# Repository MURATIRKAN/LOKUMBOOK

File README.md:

LOKUM BOOK PROJESİ
MURAT IRKAN 2024 /02
REV.A

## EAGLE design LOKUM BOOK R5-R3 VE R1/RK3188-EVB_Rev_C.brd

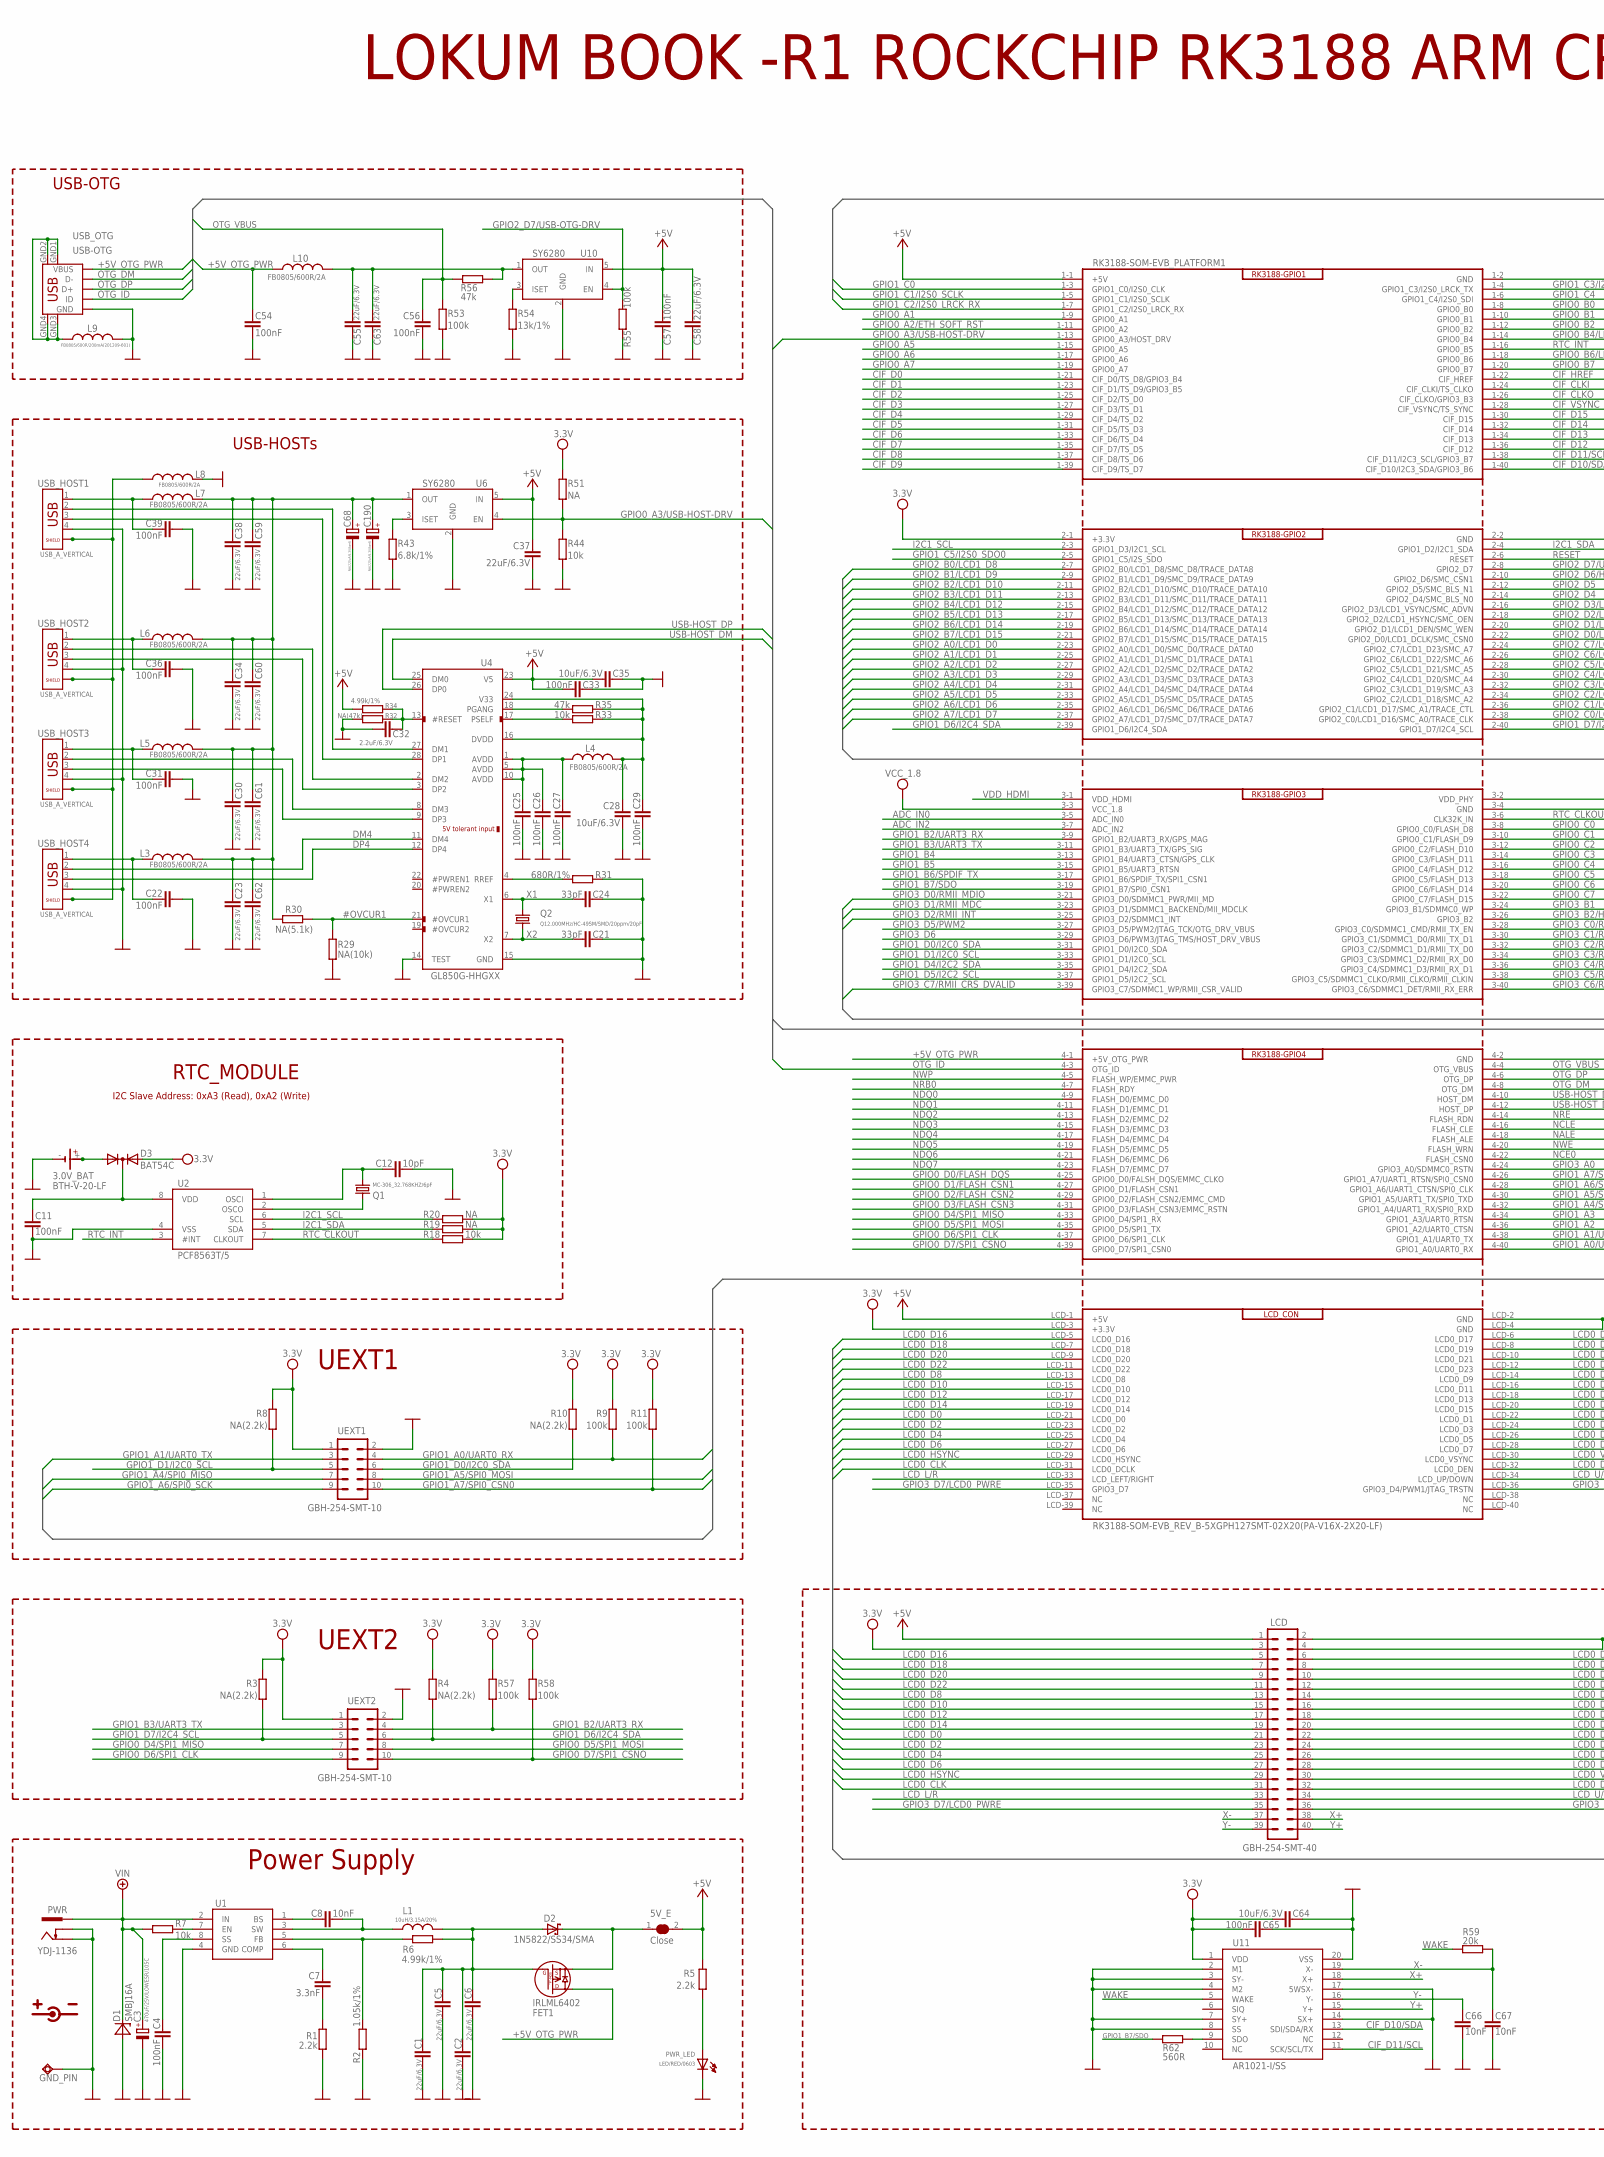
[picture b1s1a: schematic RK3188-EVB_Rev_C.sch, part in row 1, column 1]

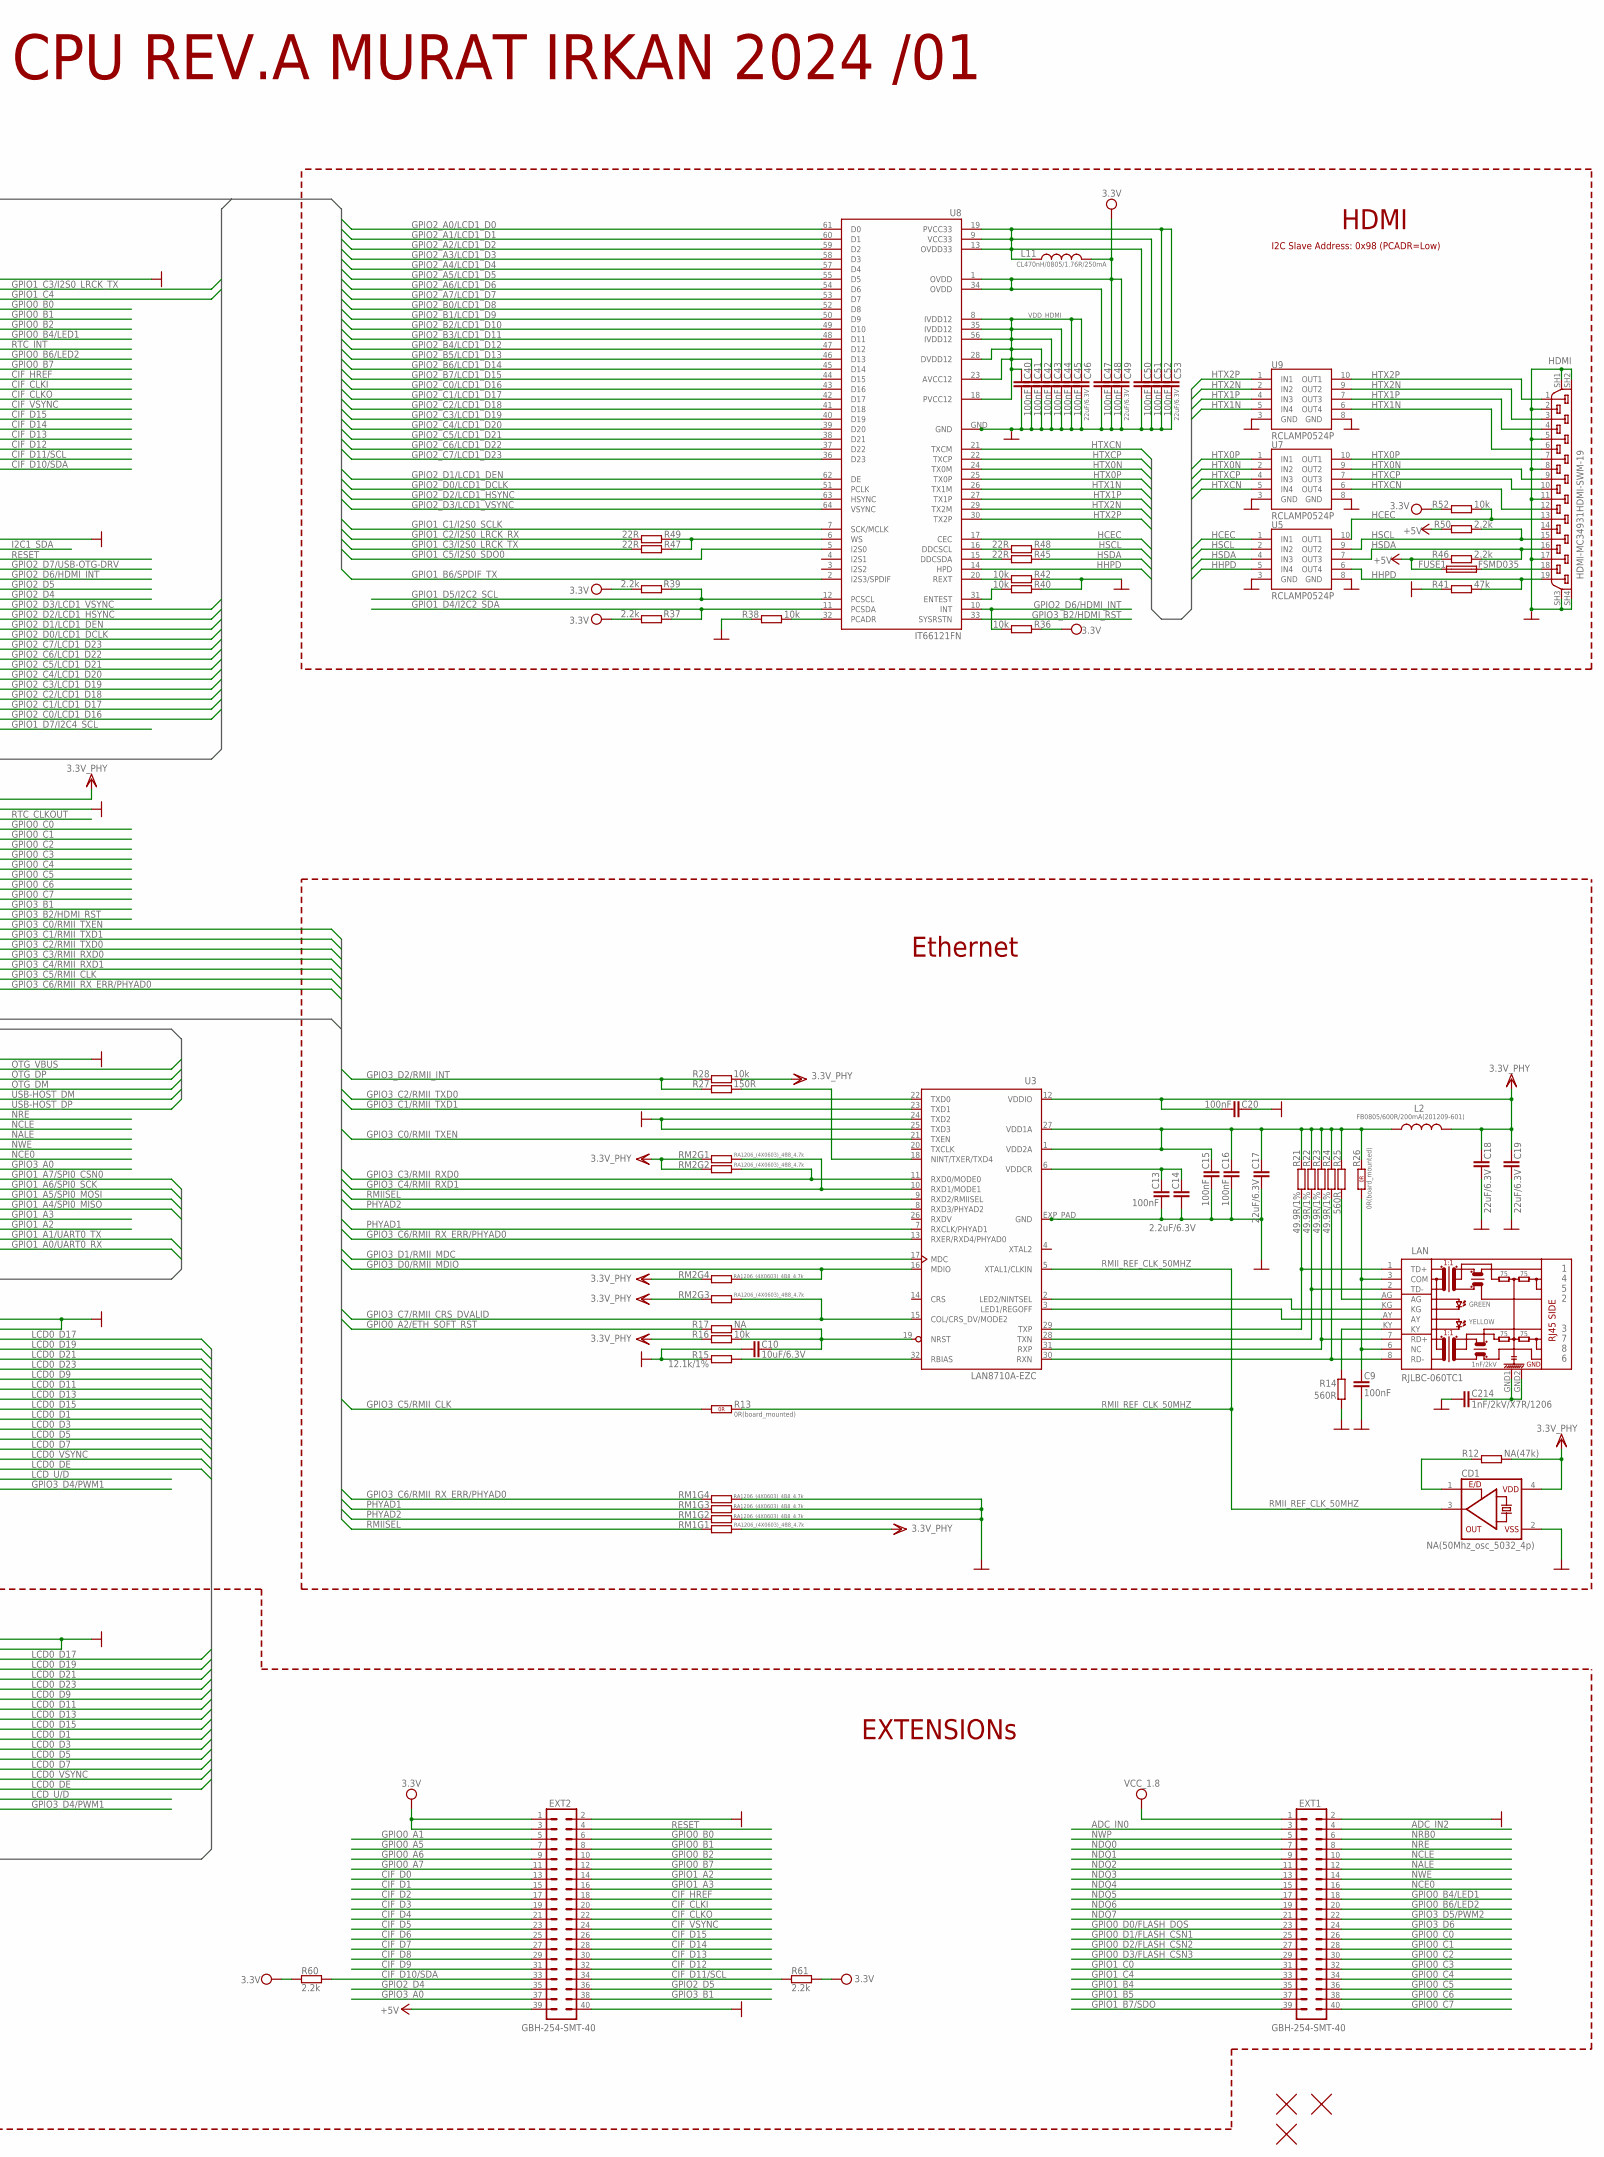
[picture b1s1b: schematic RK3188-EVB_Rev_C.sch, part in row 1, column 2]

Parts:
3.0V_BAT: BTH-V-20-LF; 3V_BAT_HOLDER
5V_E: Close; SJ-CLOSE
C1, C2, C5, C6, C17, C18, C19, C23, C30, C34, C37, C38, C46, C49, C53, C55, C58, C59, C60, C61, C62, C63: 22uF/6.3V; C0603_DWS
C3: 470uF/25V/LOWESR/105C; E5-10,5
C4, C9, C11, C13, C15, C16, C20, C22, C25, C26, C27, C29, C31, C33, C36, C39, C40, C41, C42, C43, C44, C45, C47, C48, C50, C51, C52, C54, C56, C57, C65: 100nF; C0603_DWS
C7: 3.3nF; C0603_DWS
C8, C66, C67: 10nF; C0603_DWS
C10, C28, C35, C64: 10uF/6.3V; C0603_DWS
C12: 10pF; C0603_DWS
C14, C32: 2.2uF/6.3V; C0603_DWS
C21, C24: 33pF; C0603_DWS
C68, C190: NA(220uF/6.3V/tant); CT6032
C214: 1nF/2kV/X7R/1206; C1206_5MILS_WS_ISO
CD1: NA(50Mhz_osc_5032_4p); 5032-4P_HCX-3S
D1: SMBJ16A; DO214AA
D2: 1N5822/SS34/SMA; MLL-41
D3: BAT54C; SOT23C
EXT1, EXT2: GBH-254-SMT-40; ML40-MALE(GBH-254-SMT-40)
FET1: IRLML6402; SOT23
FID1, FID3, FID4: FIDUCIAL; FIDUCIAL-1X3
FUSE1: FSMD035; 1206
GND_PIN: TESTPAD3; TEST_PAD40/70/SQUARE
HDMI: HDMI-MC34931HDMI-SWM-19; HDMI-SWM-19
L1: 10uH/3.15A/20%; 8X8MM_3131
L2, L9: FB0805/600R/200mA(201209-601); L0805_5MIL_DWS
L3, L4, L5, L6, L7, L8, L10: FB0805/600R/2A; L0805_5MIL_DWS
L11: CL470nH/0805/1.76R/250mA; L0805_5MIL_DWS
LAN: RJLBC-060TC1; RJLBC-060TC1_MILLING
LCD: GBH-254-SMT-40; ML40-MALE(GBH-254-SMT-40)
PWR: YDJ-1136; PWR_JACK_UNI_MILLING
PWR_LED: LED/RED/0603; LED-0603
Q1: MC-306_32.768KHZ/6pF; MC-306
Q2: Q12.000MHz/HC-49SM/SMD/20ppm/20pF; HC49/SMD2_THIN
R1, R5, R37, R39, R46, R50, R60, R61: 2.2k; R0603_5MIL_DWS
R2: 1.05k/1%; R0603_5MIL_DWS
R3, R4, R8, R10: NA(2.2k); R0603_5MIL_DWS
R6, R34: 4.99k/1%; R0603_5MIL_DWS
R7, R16, R18, R28, R33, R36, R38, R40, R42, R44, R52: 10k; R0603_5MIL_DWS
R9, R11, R53, R55, R57, R58: 100k; R0603_5MIL_DWS
R12, R32: NA(47k); R0603_5MIL_DWS
R13, R26: 0R(board_mounted); 0603_0R
R14, R25, R62: 560R; R0603_5MIL_DWS
R15: 12.1k/1%; R0603_5MIL_DWS
R17, R19, R20, R51: NA; R0603_5MIL_DWS
R21, R22, R23, R24: 49.9R/1%; R0603_5MIL_DWS
R27: 150R; R0603_5MIL_DWS
R29: NA(10k); R0603_5MIL_DWS
R30: NA(5.1k); R0603_5MIL_DWS
R31: 680R/1%; R0603_5MIL_DWS
R35, R41, R56: 47k; R0603_5MIL_DWS
R43: 6.8k/1%; R0603_5MIL_DWS
R45, R47, R48, R49: 22R; R0603_5MIL_DWS
R54: 13k/1%; R0603_5MIL_DWS
R59: 20k; R0603_5MIL_DWS
RK3188-SOM-EVB_PLATFORM1: RK3188-SOM-EVB_REV_B-5XGPH127SMT-02X20(PA-V16X-2X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; RK3188-SOM-EVB_REV_B
RM1, RM2: RA1206_(4X0603)_4B8_4.7k; R_MATRIX_4
U1: MP1482DS; SOIC8
U2: PCF8563T/5; SO-8
U3: LAN8710A-EZC; QFN-32(DRILLS)
U4: GL850G-HHGXX; SSOP28
U5, U7, U9: RCLAMP0524P; SLP2510P8
U6, U10: SY6280; SOT23-5
U8: IT66121FN; QFN64(IT66121FN)
U11: AR1021-I/SS; SSOP20
UEXT1, UEXT2: GBH-254-SMT-10; ML10_S
USB_HOST1, USB_HOST2, USB_HOST3, USB_HOST4: USB_A_VERTICAL; USB_A_VERTICAL_PTH
USB_OTG: USB-OTG; USB_MINI_9PIN

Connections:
#OVCUR1: R29.2, R30.1, U4.21 (#OVCUR1)
+5V: 5V_E.2, C33.1, C35.1, C37.1, C57.1, C58.1, EXT2.39, FUSE1.1, LCD.1, R5.1, R34.2, R46.2, R50.2, RK3188-SOM-EVB_PLATFORM1.1-1 (+5V), RK3188-SOM-EVB_PLATFORM1.LCD-1 (+5V), U4.23 (V5), U6.5 (IN), U10.5 (IN)
+5V_OTG_PWR: C54.1, FET1.3 (D), L10.1, RK3188-SOM-EVB_PLATFORM1.4-1 (+5V_OTG_PWR), USB_OTG.VBUS
+12V: C3.+, D1.C, PWR.+, R7.1, U1.2 (IN)
ADC_IN0: EXT1.3, RK3188-SOM-EVB_PLATFORM1.3-5 (ADC_IN0)
ADC_IN2: EXT1.4, RK3188-SOM-EVB_PLATFORM1.3-7 (ADC_IN2)
AVDD2: C25.1, C26.1, C27.1, L4.2, U4.1 (AVDD), U4.5 (AVDD), U4.10 (AVDD)
CIF_CLKI: EXT2.20, RK3188-SOM-EVB_PLATFORM1.1-24 (CIF_CLKI/TS_CLKO)
CIF_CLKO: EXT2.22, RK3188-SOM-EVB_PLATFORM1.1-26 (CIF_CLKO/GPIO3_B3)
CIF_D0: EXT2.13, RK3188-SOM-EVB_PLATFORM1.1-21 (CIF_D0/TS_D8/GPIO3_B4)
CIF_D1: EXT2.15, RK3188-SOM-EVB_PLATFORM1.1-23 (CIF_D1/TS_D9/GPIO3_B5)
CIF_D2: EXT2.17, RK3188-SOM-EVB_PLATFORM1.1-25 (CIF_D2/TS_D0)
CIF_D3: EXT2.19, RK3188-SOM-EVB_PLATFORM1.1-27 (CIF_D3/TS_D1)
CIF_D4: EXT2.21, RK3188-SOM-EVB_PLATFORM1.1-29 (CIF_D4/TS_D2)
CIF_D5: EXT2.23, RK3188-SOM-EVB_PLATFORM1.1-31 (CIF_D5/TS_D3)
CIF_D6: EXT2.25, RK3188-SOM-EVB_PLATFORM1.1-33 (CIF_D6/TS_D4)
CIF_D7: EXT2.27, RK3188-SOM-EVB_PLATFORM1.1-35 (CIF_D7/TS_D5)
CIF_D8: EXT2.29, RK3188-SOM-EVB_PLATFORM1.1-37 (CIF_D8/TS_D6)
CIF_D9: EXT2.31, RK3188-SOM-EVB_PLATFORM1.1-39 (CIF_D9/TS_D7)
CIF_D10/SDA: EXT2.33, R60.1, RK3188-SOM-EVB_PLATFORM1.1-40 (CIF_D10/I2C3_SDA/GPIO3_B6), U11.13 (SDI/SDA/RX)
CIF_D11/SCL: EXT2.34, R61.1, RK3188-SOM-EVB_PLATFORM1.1-38 (CIF_D11/I2C3_SCL/GPIO3_B7), U11.11 (SCK/SCL/TX)
CIF_D12: EXT2.32, RK3188-SOM-EVB_PLATFORM1.1-36 (CIF_D12)
CIF_D13: EXT2.30, RK3188-SOM-EVB_PLATFORM1.1-34 (CIF_D13)
CIF_D14: EXT2.28, RK3188-SOM-EVB_PLATFORM1.1-32 (CIF_D14)
CIF_D15: EXT2.26, RK3188-SOM-EVB_PLATFORM1.1-30 (CIF_D15)
CIF_HREF: EXT2.18, RK3188-SOM-EVB_PLATFORM1.1-22 (CIF_HREF)
CIF_VSYNC: EXT2.24, RK3188-SOM-EVB_PLATFORM1.1-28 (CIF_VSYNC/TS_SYNC)
DM1: U4.27 (DM1), USB_HOST1.2
DM2: U4.2 (DM2), USB_HOST2.2
DM3: U4.8 (DM3), USB_HOST3.2
DM4: U4.11 (DM4), USB_HOST4.2
DP1: U4.28 (DP1), USB_HOST1.3
DP2: U4.3 (DP2), USB_HOST2.3
DP3: U4.9 (DP3), USB_HOST3.3
DP4: U4.12 (DP4), USB_HOST4.3
DVDD1: C28.1, C29.1, L4.1, R33.1, R35.1, U4.16 (DVDD), U4.24 (V33)
GND: 3.0V_BAT.-, C1.2, C2.2, C3.-, C4.2, C5.2, C6.2, C9.1, C10.1, C11.1, C12.2, C13.1, C14.1, C15.1, C16.1, C17.1, C18.1, C19.1, C20.1, C21.1, C22.2, C23.1, C24.1, C25.2, C26.2, C27.2, C28.2, C29.2, C30.1, C31.2, C32.1, C33.2, C34.1, C35.2, C36.2, C37.2, C38.1, C39.2, C40.2, C41.2, C42.2, C43.2, C44.2, C45.2, C46.2, C47.2, C48.2, C49.2, C50.2, C51.2, C52.2, C53.2, C54.2, C55.2, C56.2, C57.2, C58.2, C59.1, C60.1, C61.1, C62.1, C63.2, C64.2, C65.2, C66.1, C67.1, C68.-, C190.-, C214.2, CD1.2 (VSS), D1.A, EXT1.2, EXT2.2, EXT2.40, GND_PIN.P$1, HDMI.2, HDMI.5, HDMI.8, HDMI.11, HDMI.17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
GPIO0_A1: EXT2.5, RK3188-SOM-EVB_PLATFORM1.1-9 (GPIO0_A1)
GPIO0_A2/ETH_SOFT_RST: R17.1, RK3188-SOM-EVB_PLATFORM1.1-11 (GPIO0_A2)
GPIO0_A3/USB-HOST-DRV: R44.2, R51.2, RK3188-SOM-EVB_PLATFORM1.1-13 (GPIO0_A3/HOST_DRV), U6.4 (EN)
GPIO0_A5: EXT2.7, RK3188-SOM-EVB_PLATFORM1.1-15 (GPIO0_A5)
GPIO0_A6: EXT2.9, RK3188-SOM-EVB_PLATFORM1.1-17 (GPIO0_A6)
GPIO0_A7: EXT2.11, RK3188-SOM-EVB_PLATFORM1.1-19 (GPIO0_A7)
GPIO0_B0: EXT2.6, RK3188-SOM-EVB_PLATFORM1.1-8 (GPIO0_B0)
GPIO0_B1: EXT2.8, RK3188-SOM-EVB_PLATFORM1.1-10 (GPIO0_B1)
GPIO0_B2: EXT2.10, RK3188-SOM-EVB_PLATFORM1.1-12 (GPIO0_B2)
GPIO0_B4/LED1: EXT1.18, RK3188-SOM-EVB_PLATFORM1.1-14 (GPIO0_B4)
GPIO0_B6/LED2: EXT1.20, RK3188-SOM-EVB_PLATFORM1.1-18 (GPIO0_B6)
GPIO0_B7: EXT2.12, RK3188-SOM-EVB_PLATFORM1.1-20 (GPIO0_B7)
GPIO0_C0: EXT1.26, RK3188-SOM-EVB_PLATFORM1.3-8 (GPIO0_C0/FLASH_D8)
GPIO0_C1: EXT1.28, RK3188-SOM-EVB_PLATFORM1.3-10 (GPIO0_C1/FLASH_D9)
GPIO0_C2: EXT1.30, RK3188-SOM-EVB_PLATFORM1.3-12 (GPIO0_C2/FLASH_D10)
GPIO0_C3: EXT1.32, RK3188-SOM-EVB_PLATFORM1.3-14 (GPIO0_C3/FLASH_D11)
GPIO0_C4: EXT1.34, RK3188-SOM-EVB_PLATFORM1.3-16 (GPIO0_C4/FLASH_D12)
GPIO0_C5: EXT1.36, RK3188-SOM-EVB_PLATFORM1.3-18 (GPIO0_C5/FLASH_D13)
GPIO0_C6: EXT1.38, RK3188-SOM-EVB_PLATFORM1.3-20 (GPIO0_C6/FLASH_D14)
GPIO0_C7: EXT1.40, RK3188-SOM-EVB_PLATFORM1.3-22 (GPIO0_C7/FLASH_D15)
GPIO0_D0/FLASH_DQS: EXT1.23, RK3188-SOM-EVB_PLATFORM1.4-25 (GPIO0_D0/FALSH_DQS/EMMC_CLKO)
GPIO0_D1/FLASH_CSN1: EXT1.25, RK3188-SOM-EVB_PLATFORM1.4-27 (GPIO0_D1/FLASH_CSN1)
GPIO0_D2/FLASH_CSN2: EXT1.27, RK3188-SOM-EVB_PLATFORM1.4-29 (GPIO0_D2/FLASH_CSN2/EMMC_CMD)
GPIO0_D3/FLASH_CSN3: EXT1.29, RK3188-SOM-EVB_PLATFORM1.4-31 (GPIO0_D3/FLASH_CSN3/EMMC_RSTN)
GPIO0_D4/SPI1_MISO: RK3188-SOM-EVB_PLATFORM1.4-33 (GPIO0_D4/SPI1_RX), UEXT2.7
GPIO0_D5/SPI1_MOSI: RK3188-SOM-EVB_PLATFORM1.4-35 (GPIO0_D5/SPI1_TX), UEXT2.8
GPIO0_D6/SPI1_CLK: RK3188-SOM-EVB_PLATFORM1.4-37 (GPIO0_D6/SPI1_CLK), UEXT2.9
GPIO0_D7/SPI1_CSNO: R58.1, RK3188-SOM-EVB_PLATFORM1.4-39 (GPIO0_D7/SPI1_CSN0), UEXT2.10
GPIO1_A0/UART0_RX: R9.1, RK3188-SOM-EVB_PLATFORM1.4-40 (GPIO1_A0/UART0_RX), UEXT1.4
GPIO1_A1/UART0_TX: RK3188-SOM-EVB_PLATFORM1.4-38 (GPIO1_A1/UART0_TX), UEXT1.3
GPIO1_A2: EXT2.14, RK3188-SOM-EVB_PLATFORM1.4-36 (GPIO1_A2/UART0_CTSN)
GPIO1_A3: EXT2.16, RK3188-SOM-EVB_PLATFORM1.4-34 (GPIO1_A3/UART0_RTSN)
GPIO1_A4/SPI0_MISO: RK3188-SOM-EVB_PLATFORM1.4-32 (GPIO1_A4/UART1_RX/SPI0_RXD), UEXT1.7
GPIO1_A5/SPI0_MOSI: RK3188-SOM-EVB_PLATFORM1.4-30 (GPIO1_A5/UART1_TX/SPI0_TXD), UEXT1.8
GPIO1_A6/SPI0_SCK: RK3188-SOM-EVB_PLATFORM1.4-28 (GPIO1_A6/UART1_CTSN/SPI0_CLK), UEXT1.9
GPIO1_A7/SPI0_CSN0: R11.1, RK3188-SOM-EVB_PLATFORM1.4-26 (GPIO1_A7/UART1_RTSN/SPI0_CSN0), UEXT1.10
GPIO1_B2/UART3_RX: R57.1, RK3188-SOM-EVB_PLATFORM1.3-9 (GPIO1_B2/UART3_RX/GPS_MAG), UEXT2.4
GPIO1_B3/UART3_TX: RK3188-SOM-EVB_PLATFORM1.3-11 (GPIO1_B3/UART3_TX/GPS_SIG), UEXT2.3
GPIO1_B4: EXT1.35, RK3188-SOM-EVB_PLATFORM1.3-13 (GPIO1_B4/UART3_CTSN/GPS_CLK)
GPIO1_B5: EXT1.37, RK3188-SOM-EVB_PLATFORM1.3-15 (GPIO1_B5/UART3_RTSN)
GPIO1_B6/SPDIF_TX: RK3188-SOM-EVB_PLATFORM1.3-17 (GPIO1_B6/SPDIF_TX/SPI1_CSN1), U8.2 (I2S3/SPDIF)
GPIO1_B7/SDO: EXT1.39, R62.2, RK3188-SOM-EVB_PLATFORM1.3-19 (GPIO1_B7/SPI0_CSN1)
GPIO1_C0: EXT1.31, RK3188-SOM-EVB_PLATFORM1.1-3 (GPIO1_C0/I2S0_CLK)
GPIO1_C1/I2S0_SCLK: RK3188-SOM-EVB_PLATFORM1.1-5 (GPIO1_C1/I2S0_SCLK), U8.7 (SCK/MCLK)
GPIO1_C2/I2S0_LRCK_RX: R49.1, RK3188-SOM-EVB_PLATFORM1.1-7 (GPIO1_C2/I2S0_LRCK_RX)
GPIO1_C3/I2S0_LRCK_TX: R47.1, RK3188-SOM-EVB_PLATFORM1.1-4 (GPIO1_C3/I2S0_LRCK_TX)
GPIO1_C4: EXT1.33, RK3188-SOM-EVB_PLATFORM1.1-6 (GPIO1_C4/I2S0_SDI)
GPIO1_C5/I2S0_SDO0: RK3188-SOM-EVB_PLATFORM1.2-5 (GPIO1_C5/I2S_SDO), U8.5 (I2S0)
GPIO1_D0/I2C0_SDA: R10.1, RK3188-SOM-EVB_PLATFORM1.3-31 (GPIO1_D0/I2C0_SDA), UEXT1.6
GPIO1_D1/I2C0_SCL: R8.1, RK3188-SOM-EVB_PLATFORM1.3-33 (GPIO1_D1/I2C0_SCL), UEXT1.5
GPIO1_D4/I2C2_SDA: R37.1, RK3188-SOM-EVB_PLATFORM1.3-35 (GPIO1_D4/I2C2_SDA), U8.11 (PCSDA)
GPIO1_D5/I2C2_SCL: R39.1, RK3188-SOM-EVB_PLATFORM1.3-37 (GPIO1_D5/I2C2_SCL), U8.12 (PCSCL)
GPIO1_D6/I2C4_SDA: R4.1, RK3188-SOM-EVB_PLATFORM1.2-39 (GPIO1_D6/I2C4_SDA), UEXT2.6
GPIO1_D7/I2C4_SCL: R3.1, RK3188-SOM-EVB_PLATFORM1.2-40 (GPIO1_D7/I2C4_SCL), UEXT2.5
GPIO2_A0/LCD1_D0: RK3188-SOM-EVB_PLATFORM1.2-23 (GPIO2_A0/LCD1_D0/SMC_D0/TRACE_DATA0), U8.61 (D0)
GPIO2_A1/LCD1_D1: RK3188-SOM-EVB_PLATFORM1.2-25 (GPIO2_A1/LCD1_D1/SMC_D1/TRACE_DATA1), U8.60 (D1)
GPIO2_A2/LCD1_D2: RK3188-SOM-EVB_PLATFORM1.2-27 (GPIO2_A2/LCD1_D2/SMC_D2/TRACE_DATA2), U8.59 (D2)
GPIO2_A3/LCD1_D3: RK3188-SOM-EVB_PLATFORM1.2-29 (GPIO2_A3/LCD1_D3/SMC_D3/TRACE_DATA3), U8.58 (D3)
GPIO2_A4/LCD1_D4: RK3188-SOM-EVB_PLATFORM1.2-31 (GPIO2_A4/LCD1_D4/SMC_D4/TRACE_DATA4), U8.57 (D4)
GPIO2_A5/LCD1_D5: RK3188-SOM-EVB_PLATFORM1.2-33 (GPIO2_A5/LCD1_D5/SMC_D5/TRACE_DATA5), U8.55 (D5)
GPIO2_A6/LCD1_D6: RK3188-SOM-EVB_PLATFORM1.2-35 (GPIO2_A6/LCD1_D6/SMC_D6/TRACE_DATA6), U8.54 (D6)
GPIO2_A7/LCD1_D7: RK3188-SOM-EVB_PLATFORM1.2-37 (GPIO2_A7/LCD1_D7/SMC_D7/TRACE_DATA7), U8.53 (D7)
GPIO2_B0/LCD1_D8: RK3188-SOM-EVB_PLATFORM1.2-7 (GPIO2_B0/LCD1_D8/SMC_D8/TRACE_DATA8), U8.52 (D8)
GPIO2_B1/LCD1_D9: RK3188-SOM-EVB_PLATFORM1.2-9 (GPIO2_B1/LCD1_D9/SMC_D9/TRACE_DATA9), U8.50 (D9)
GPIO2_B2/LCD1_D10: RK3188-SOM-EVB_PLATFORM1.2-11 (GPIO2_B2/LCD1_D10/SMC_D10/TRACE_DATA10), U8.49 (D10)
GPIO2_B3/LCD1_D11: RK3188-SOM-EVB_PLATFORM1.2-13 (GPIO2_B3/LCD1_D11/SMC_D11/TRACE_DATA11), U8.48 (D11)
GPIO2_B4/LCD1_D12: RK3188-SOM-EVB_PLATFORM1.2-15 (GPIO2_B4/LCD1_D12/SMC_D12/TRACE_DATA12), U8.47 (D12)
GPIO2_B5/LCD1_D13: RK3188-SOM-EVB_PLATFORM1.2-17 (GPIO2_B5/LCD1_D13/SMC_D13/TRACE_DATA13), U8.46 (D13)
GPIO2_B6/LCD1_D14: RK3188-SOM-EVB_PLATFORM1.2-19 (GPIO2_B6/LCD1_D14/SMC_D14/TRACE_DATA14), U8.45 (D14)
GPIO2_B7/LCD1_D15: RK3188-SOM-EVB_PLATFORM1.2-21 (GPIO2_B7/LCD1_D15/SMC_D15/TRACE_DATA15), U8.44 (D15)
GPIO2_C0/LCD1_D16: RK3188-SOM-EVB_PLATFORM1.2-38 (GPIO2_C0/LCD1_D16/SMC_A0/TRACE_CLK), U8.43 (D16)
GPIO2_C1/LCD1_D17: RK3188-SOM-EVB_PLATFORM1.2-36 (GPIO2_C1/LCD1_D17/SMC_A1/TRACE_CTL), U8.42 (D17)
GPIO2_C2/LCD1_D18: RK3188-SOM-EVB_PLATFORM1.2-34 (GPIO2_C2/LCD1_D18/SMC_A2), U8.41 (D18)
GPIO2_C3/LCD1_D19: RK3188-SOM-EVB_PLATFORM1.2-32 (GPIO2_C3/LCD1_D19/SMC_A3), U8.40 (D19)
GPIO2_C4/LCD1_D20: RK3188-SOM-EVB_PLATFORM1.2-30 (GPIO2_C4/LCD1_D20/SMC_A4), U8.39 (D20)
GPIO2_C5/LCD1_D21: RK3188-SOM-EVB_PLATFORM1.2-28 (GPIO2_C5/LCD1_D21/SMC_A5), U8.38 (D21)
GPIO2_C6/LCD1_D22: RK3188-SOM-EVB_PLATFORM1.2-26 (GPIO2_C6/LCD1_D22/SMC_A6), U8.37 (D22)
GPIO2_C7/LCD1_D23: RK3188-SOM-EVB_PLATFORM1.2-24 (GPIO2_C7/LCD1_D23/SMC_A7), U8.36 (D23)
GPIO2_D0/LCD1_DCLK: RK3188-SOM-EVB_PLATFORM1.2-22 (GPIO2_D0/LCD1_DCLK/SMC_CSN0), U8.51 (PCLK)
GPIO2_D1/LCD1_DEN: RK3188-SOM-EVB_PLATFORM1.2-20 (GPIO2_D1/LCD1_DEN/SMC_WEN), U8.62 (DE)
GPIO2_D2/LCD1_HSYNC: RK3188-SOM-EVB_PLATFORM1.2-18 (GPIO2_D2/LCD1_HSYNC/SMC_OEN), U8.63 (HSYNC)
GPIO2_D3/LCD1_VSYNC: RK3188-SOM-EVB_PLATFORM1.2-16 (GPIO2_D3/LCD1_VSYNC/SMC_ADVN), U8.64 (VSYNC)
GPIO2_D4: EXT2.35, RK3188-SOM-EVB_PLATFORM1.2-14 (GPIO2_D4/SMC_BLS_N0)
GPIO2_D5: EXT2.36, RK3188-SOM-EVB_PLATFORM1.2-12 (GPIO2_D5/SMC_BLS_N1)
GPIO2_D6/HDMI_INT: R36.1, RK3188-SOM-EVB_PLATFORM1.2-10 (GPIO2_D6/SMC_CSN1), U8.10 (INT)
GPIO2_D7/USB-OTG-DRV: R55.2, RK3188-SOM-EVB_PLATFORM1.2-8 (GPIO2_D7), U10.4 (EN)
GPIO3_A0: EXT2.37, RK3188-SOM-EVB_PLATFORM1.4-24 (GPIO3_A0/SDMMC0_RSTN)
GPIO3_B1: EXT2.38, RK3188-SOM-EVB_PLATFORM1.3-24 (GPIO3_B1/SDMMC0_WP)
GPIO3_B2/HDMI_RST: RK3188-SOM-EVB_PLATFORM1.3-26 (GPIO3_B2), U8.33 (SYSRSTN)
GPIO3_C0/RMII_TXEN: RK3188-SOM-EVB_PLATFORM1.3-28 (GPIO3_C0/SDMMC1_CMD/RMII_TX_EN), U3.21 (TXEN)
GPIO3_C1/RMII_TXD1: RK3188-SOM-EVB_PLATFORM1.3-30 (GPIO3_C1/SDMMC1_D0/RMII_TX_D1), U3.23 (TXD1)
GPIO3_C2/RMII_TXD0: RK3188-SOM-EVB_PLATFORM1.3-32 (GPIO3_C2/SDMMC1_D1/RMII_TX_D0), U3.22 (TXD0)
GPIO3_C3/RMII_RXD0: RK3188-SOM-EVB_PLATFORM1.3-34 (GPIO3_C3/SDMMC1_D2/RMII_RX_D0), RM2.2.2 (2), U3.11 (RXD0/MODE0)
GPIO3_C4/RMII_RXD1: RK3188-SOM-EVB_PLATFORM1.3-36 (GPIO3_C4/SDMMC1_D3/RMII_RX_D1), RM2.1.2 (2), U3.10 (RXD1/MODE1)
GPIO3_C5/RMII_CLK: R13.1 (1.1), RK3188-SOM-EVB_PLATFORM1.3-38 (GPIO3_C5/SDMMC1_CLKO/RMII_CLKO/RMII_CLK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)
GPIO3_C6/RMII_RX_ERR/PHYAD0: RK3188-SOM-EVB_PLATFORM1.3-40 (GPIO3_C6/SDMMC1_DET/RMII_RX_ERR), RM1.4.1 (1), U3.13 (RXER/RXD4/PHYAD0)
GPIO3_C7/RMII_CRS_DVALID: RK3188-SOM-EVB_PLATFORM1.3-39 (GPIO3_C7/SDMMC1_WP/RMII_CSR_VALID), RM2.3.2 (2), U3.15 (COL/CRS_DV/MODE2)
GPIO3_D0/RMII_MDIO: RK3188-SOM-EVB_PLATFORM1.3-21 (GPIO3_D0/SDMMC1_PWR/MII_MD), RM2.4.2 (2), U3.16 (MDIO)
GPIO3_D1/RMII_MDC: RK3188-SOM-EVB_PLATFORM1.3-23 (GPIO3_D1/SDMMC1_BACKEND/MII_MDCLK), U3.17 (MDC)
GPIO3_D2/RMII_INT: R27.1, R28.1, RK3188-SOM-EVB_PLATFORM1.3-25 (GPIO3_D2/SDMMC1_INT)
GPIO3_D4/PWM1: LCD.36, RK3188-SOM-EVB_PLATFORM1.LCD-36 (GPIO3_D4/PWM1/JTAG_TRSTN)
GPIO3_D5/PWM2: EXT1.22, RK3188-SOM-EVB_PLATFORM1.3-27 (GPIO3_D5/PWM2/JTAG_TCK/OTG_DRV_VBUS)
GPIO3_D6: EXT1.24, RK3188-SOM-EVB_PLATFORM1.3-29 (GPIO3_D6/PWM3/JTAG_TMS/HOST_DRV_VBUS)
GPIO3_D7/LCD0_PWRE: LCD.35, RK3188-SOM-EVB_PLATFORM1.LCD-35 (GPIO3_D7)
HCEC: HDMI.13, R52.1, U5.1 (IN1), U5.10 (OUT1), U8.17 (CEC)
HDMI_5V_SOURCE: FUSE1.2, HDMI.18
HHPD: HDMI.19, R41.1, U5.5 (IN4), U5.6 (OUT4), U8.14 (HPD)
HSCL: HDMI.15, R48.1, R50.1, U5.2 (IN2), U5.9 (OUT2)
HSDA: HDMI.16, R45.1, R46.1, U5.4 (IN3), U5.7 (OUT3)
HTX0N: HDMI.9, U7.2 (IN2), U7.9 (OUT2), U8.24 (TX0M)
HTX0P: HDMI.7, U7.1 (IN1), U7.10 (OUT1), U8.25 (TX0P)
HTX1N: HDMI.6, U8.26 (TX1M), U9.5 (IN4), U9.6 (OUT4)
HTX1P: HDMI.4, U8.27 (TX1P), U9.4 (IN3), U9.7 (OUT3)
HTX2N: HDMI.3, U8.29 (TX2M), U9.2 (IN2), U9.9 (OUT2)
HTX2P: HDMI.1, U8.30 (TX2P), U9.1 (IN1), U9.10 (OUT1)
HTXCN: HDMI.12, U7.5 (IN4), U7.6 (OUT4), U8.21 (TXCM)
HTXCP: HDMI.10, U7.4 (IN3), U7.7 (OUT3), U8.22 (TXCP)
I2C1_SCL: R20.1, RK3188-SOM-EVB_PLATFORM1.2-3 (GPIO1_D3/I2C1_SCL), U2.6 (SCL)
I2C1_SDA: R19.1, RK3188-SOM-EVB_PLATFORM1.2-4 (GPIO1_D2/I2C1_SDA), U2.5 (SDA)
I2S0_LRCK: R47.2, R49.2, U8.6 (WS)
LCD0_CLK: LCD.31, RK3188-SOM-EVB_PLATFORM1.LCD-31 (LCD0_DCLK)
LCD0_D0: LCD.21, RK3188-SOM-EVB_PLATFORM1.LCD-21 (LCD0_D0)
LCD0_D1: LCD.22, RK3188-SOM-EVB_PLATFORM1.LCD-22 (LCD0_D1)
LCD0_D2: LCD.23, RK3188-SOM-EVB_PLATFORM1.LCD-23 (LCD0_D2)
LCD0_D3: LCD.24, RK3188-SOM-EVB_PLATFORM1.LCD-24 (LCD0_D3)
LCD0_D4: LCD.25, RK3188-SOM-EVB_PLATFORM1.LCD-25 (LCD0_D4)
LCD0_D5: LCD.26, RK3188-SOM-EVB_PLATFORM1.LCD-26 (LCD0_D5)
LCD0_D6: LCD.27, RK3188-SOM-EVB_PLATFORM1.LCD-27 (LCD0_D6)
LCD0_D7: LCD.28, RK3188-SOM-EVB_PLATFORM1.LCD-28 (LCD0_D7)
LCD0_D8: LCD.13, RK3188-SOM-EVB_PLATFORM1.LCD-13 (LCD0_D8)
LCD0_D9: LCD.14, RK3188-SOM-EVB_PLATFORM1.LCD-14 (LCD0_D9)
LCD0_D10: LCD.15, RK3188-SOM-EVB_PLATFORM1.LCD-15 (LCD0_D10)
LCD0_D11: LCD.16, RK3188-SOM-EVB_PLATFORM1.LCD-16 (LCD0_D11)
LCD0_D12: LCD.17, RK3188-SOM-EVB_PLATFORM1.LCD-17 (LCD0_D12)
LCD0_D13: LCD.18, RK3188-SOM-EVB_PLATFORM1.LCD-18 (LCD0_D13)
LCD0_D14: LCD.19, RK3188-SOM-EVB_PLATFORM1.LCD-19 (LCD0_D14)
LCD0_D15: LCD.20, RK3188-SOM-EVB_PLATFORM1.LCD-20 (LCD0_D15)
LCD0_D16: LCD.5, RK3188-SOM-EVB_PLATFORM1.LCD-5 (LCD0_D16)
LCD0_D17: LCD.6, RK3188-SOM-EVB_PLATFORM1.LCD-6 (LCD0_D17)
LCD0_D18: LCD.7, RK3188-SOM-EVB_PLATFORM1.LCD-7 (LCD0_D18)
LCD0_D19: LCD.8, RK3188-SOM-EVB_PLATFORM1.LCD-8 (LCD0_D19)
LCD0_D20: LCD.9, RK3188-SOM-EVB_PLATFORM1.LCD-9 (LCD0_D20)
LCD0_D21: LCD.10, RK3188-SOM-EVB_PLATFORM1.LCD-10 (LCD0_D21)
LCD0_D22: LCD.11, RK3188-SOM-EVB_PLATFORM1.LCD-11 (LCD0_D22)
LCD0_D23: LCD.12, RK3188-SOM-EVB_PLATFORM1.LCD-12 (LCD0_D23)
LCD0_DE: LCD.32, RK3188-SOM-EVB_PLATFORM1.LCD-32 (LCD0_DEN)
LCD0_HSYNC: LCD.29, RK3188-SOM-EVB_PLATFORM1.LCD-29 (LCD0_HSYNC)
LCD0_VSYNC: LCD.30, RK3188-SOM-EVB_PLATFORM1.LCD-30 (LCD0_VSYNC)
LCD_L/R: LCD.33, RK3188-SOM-EVB_PLATFORM1.LCD-33 (LCD_LEFT/RIGHT)
LCD_U/D: LCD.34, RK3188-SOM-EVB_PLATFORM1.LCD-34 (LCD_UP/DOWN)
unnamed: R62.1, U11.9 (SDO)
unnamed: C214.1, LAN.GND1, LAN.GND2
unnamed: CD1.1 (E/D), R12.2
unnamed: LAN.2 (TD-), R22.1, U3.28 (TXN)
unnamed: LAN.KG, U3.2 (LED2/NINTSEL)
unnamed: C13.2, C14.2, U3.6 (VDDCR)
unnamed: C10.2, R16.2, R17.2, U3.19 (NRST)
unnamed: R43.2, U6.3 (ISET)
unnamed: R31.2, U4.4 (RREF)
unnamed: C39.1, L7.2, USB_HOST1.1
unnamed: R42.1, U8.20 (REXT)
unnamed: R40.1, U8.31 (ENTEST)
unnamed: C32.2, R32.1, R34.1, U4.13 (#RESET)
unnamed: L8.2, USB_HOST1.P$3 (5), USB_HOST1.P$4 (6), USB_HOST2.P$3 (5), USB_HOST2.P$4 (6), USB_HOST3.P$3 (5), USB_HOST3.P$4 (6), USB_HOST4.P$3 (5), USB_HOST4.P$4 (6)
unnamed: C22.1, L3.2, USB_HOST4.1
unnamed: C23.2, C30.2, C34.2, C38.2, C59.2, C60.2, C61.2, C62.2, C68.+, C190.+, L3.1, L5.1, L6.1, L7.1, R30.2, U6.1 (OUT)
unnamed: LAN.1 (TD+), R21.1, U3.29 (TXP)
unnamed: LAN.7 (RD+), R23.1, U3.31 (RXP)
unnamed: C4.1, U1.8 (SS)
unnamed: R7.2, U1.7 (EN)
unnamed: C36.1, L6.2, USB_HOST2.1
unnamed: C31.1, L5.2, USB_HOST3.1
unnamed: LAN.8 (RD-), R24.1, U3.30 (RXN)
unnamed: R33.2, U4.17 (PSELF)
unnamed: C8.1, U1.1 (BS)
unnamed: C8.2, L1.1, U1.3 (SW)
unnamed: C50.1, C51.1, C52.1, C53.1, L11.2, U8.9 (VCC33), U8.13 (OVDD33), U8.19 (PVCC33)
unnamed: LAN.AY, U3.3 (LED1/REGOFF)
unnamed: R15.2, U3.32 (RBIAS)
unnamed: C9.2, LAN.3 (COM), LAN.6 (NC), R26.1 (1.1)
unnamed: LAN.KY, R14.1
unnamed: C15.2, C16.2, C17.2, L2.1, R21.2, R22.2, R23.2, R24.2, R25.1, R26.2 (1.2), U3.1 (VDD2A), U3.27 (VDD1A)
unnamed: C7.1, U1.6 (COMP)
unnamed: R48.2, U8.16 (DDCSCL)
unnamed: R45.2, U8.15 (DDCSDA)
unnamed: R27.2, U3.18 (NINT/TXER/TXD4)
unnamed: C7.2, R1.1
unnamed: LAN.AG, R25.2
unnamed: R2.1, R6.1, U1.5 (FB)
unnamed: C1.1, C2.1, C5.1, C6.1, D2.A, FET1.1 (G), L1.2, R6.2
unnamed: 5V_E.1, D2.K (C), FET1.2 (S)
unnamed: R38.1, U8.32 (PCADR)
unnamed: R35.2, U4.18 (PGANG)
unnamed: R54.2, U10.3 (ISET)
unnamed: C12.1, Q1.1, U2.1 (OSCI)
unnamed: PWR_LED.A, R5.2
unnamed: Q1.4 (2), U2.2 (OSCO)
unnamed: 3.0V_BAT.1+ (+), 3.0V_BAT.+, D3.2 (A2)
unnamed: C55.1, C63.1, L10.2, R56.2, U10.1 (OUT)
unnamed: L9.2, USB_OTG.GND1, USB_OTG.GND2, USB_OTG.GND3, USB_OTG.GND4
NALE: EXT1.12, RK3188-SOM-EVB_PLATFORM1.4-18 (FLASH_ALE)
NCE0: EXT1.16, RK3188-SOM-EVB_PLATFORM1.4-22 (FLASH_CSN0)
NCLE: EXT1.10, RK3188-SOM-EVB_PLATFORM1.4-16 (FLASH_CLE)
NDQ0: EXT1.7, RK3188-SOM-EVB_PLATFORM1.4-9 (FLASH_D0/EMMC_D0)
NDQ1: EXT1.9, RK3188-SOM-EVB_PLATFORM1.4-11 (FLASH_D1/EMMC_D1)
NDQ2: EXT1.11, RK3188-SOM-EVB_PLATFORM1.4-13 (FLASH_D2/EMMC_D2)
NDQ3: EXT1.13, RK3188-SOM-EVB_PLATFORM1.4-15 (FLASH_D3/EMMC_D3)
NDQ4: EXT1.15, RK3188-SOM-EVB_PLATFORM1.4-17 (FLASH_D4/EMMC_D4)
NDQ5: EXT1.17, RK3188-SOM-EVB_PLATFORM1.4-19 (FLASH_D5/EMMC_D5)
NDQ6: EXT1.19, RK3188-SOM-EVB_PLATFORM1.4-21 (FLASH_D6/EMMC_D6)
NDQ7: EXT1.21, RK3188-SOM-EVB_PLATFORM1.4-23 (FLASH_D7/EMMC_D7)
NRB0: EXT1.6, RK3188-SOM-EVB_PLATFORM1.4-7 (FLASH_RDY)
NRE: EXT1.8, RK3188-SOM-EVB_PLATFORM1.4-14 (FLASH_RDN)
NWE: EXT1.14, RK3188-SOM-EVB_PLATFORM1.4-20 (FLASH_WRN)
NWP: EXT1.5, RK3188-SOM-EVB_PLATFORM1.4-5 (FLASH_WP/EMMC_PWR)
OTG_DM: RK3188-SOM-EVB_PLATFORM1.4-8 (OTG_DM), USB_OTG.D-
OTG_DP: RK3188-SOM-EVB_PLATFORM1.4-6 (OTG_DP), USB_OTG.D+
OTG_ID: RK3188-SOM-EVB_PLATFORM1.4-3 (OTG_ID), USB_OTG.ID
OTG_VBUS: C56.1, R53.2, R56.1, RK3188-SOM-EVB_PLATFORM1.4-4 (OTG_VBUS)
PHYAD1: RM1.3.1 (1), U3.7 (RXCLK/PHYAD1)
PHYAD2: RM1.2.1 (1), U3.8 (RXD3/PHYAD2)
RESET: EXT2.4, RK3188-SOM-EVB_PLATFORM1.2-6 (RESET)
RMIISEL: RM1.1.1 (1), U3.9 (RXD2/RMIISEL)
RMII_REF_CLK_50MHZ: CD1.3 (OUT), R13.2 (1.2), U3.5 (XTAL1/CLKIN)
RTC_CLKOUT: R18.1, RK3188-SOM-EVB_PLATFORM1.3-6 (CLK32K_IN), U2.7 (CLKOUT)
RTC_INT: RK3188-SOM-EVB_PLATFORM1.1-16 (GPIO0_B5), U2.3 (#INT)
RTC_VDD: C11.2, D3.3 (K), U2.8 (VDD)
USB-HOST_DM: RK3188-SOM-EVB_PLATFORM1.4-10 (HOST_DM), U4.25 (DM0)
USB-HOST_DP: RK3188-SOM-EVB_PLATFORM1.4-12 (HOST_DP), U4.26 (DP0)
VCC: C47.1, C48.1, C49.1, C64.1, C65.1, D3.1 (A1), EXT2.1, EXT2.3, L11.1, LCD.3, R3.2, R4.2, R8.2, R9.2, R10.2, R11.2, R18.2, R19.2, R20.2, R36.2, R37.2, R39.2, R51.1, R52.2, R57.2, R58.2, R60.2, R61.2, RK3188-SOM-EVB_PLATFORM1.2-1 (+3.3V), RK3188-SOM-EVB_PLATFORM1.LCD-3 (+3.3V), U8.1 (OVDD), U8.34 (OVDD), U11.1 (VDD), UEXT1.1, UEXT2.1
VDD: C18.2, C19.2, C20.2, CD1.4 (VDD), L2.2, R12.1, R16.1, R28.2, RK3188-SOM-EVB_PLATFORM1.3-2 (VDD_PHY), RM1.1.2 (2), RM2.1.1 (1), RM2.2.1 (1), RM2.3.1 (1), RM2.4.1 (1), U3.12 (VDDIO)
VDD_HDMI: C40.1, C41.1, C42.1, C43.1, C44.1, C45.1, C46.1, RK3188-SOM-EVB_PLATFORM1.3-1 (VDD_HDMI), U8.8 (IVDD12), U8.18 (PVCC12), U8.23 (AVCC12), U8.28 (DVDD12), U8.35 (IVDD12), U8.56 (IVDD12)
VPP: EXT1.1, RK3188-SOM-EVB_PLATFORM1.3-3 (VCC_1.8)
WAKE: R59.1, U11.5 (WAKE)
X1: C24.2, Q2.2, U4.6 (X1)
X2: C21.2, Q2.1, U4.7 (X2)
X+: LCD.38, U11.18 (X+)
X-: C67.2, LCD.37, R59.2, U11.19 (X-)
Y+: LCD.40, U11.15 (Y+)
Y-: C66.2, LCD.39, U11.16 (Y-)

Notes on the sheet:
EXTENSIONs
RTC_MODULE
USB-OTG
HDMI
Ethernet
I2C Slave Address: 0x98 (PCADR=Low)
USB-HOSTs
Power Supply
I2C Slave Address: 0xA3 (Read), 0xA2 (Write)
UEXT1
UEXT2
LOKUM BOOK -R1 ROCKCHIP RK3188 ARM CPU REV.A MURAT IRKAN 2024 /01

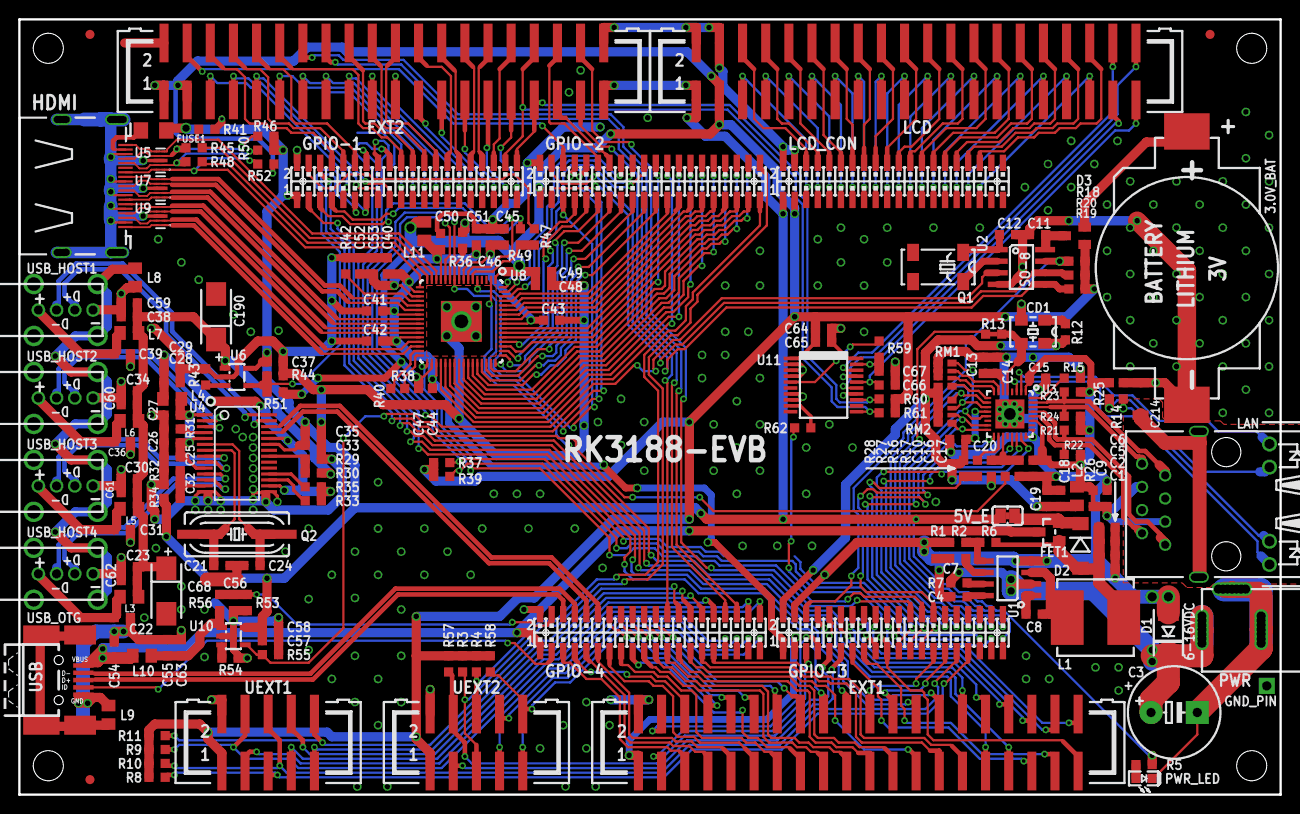
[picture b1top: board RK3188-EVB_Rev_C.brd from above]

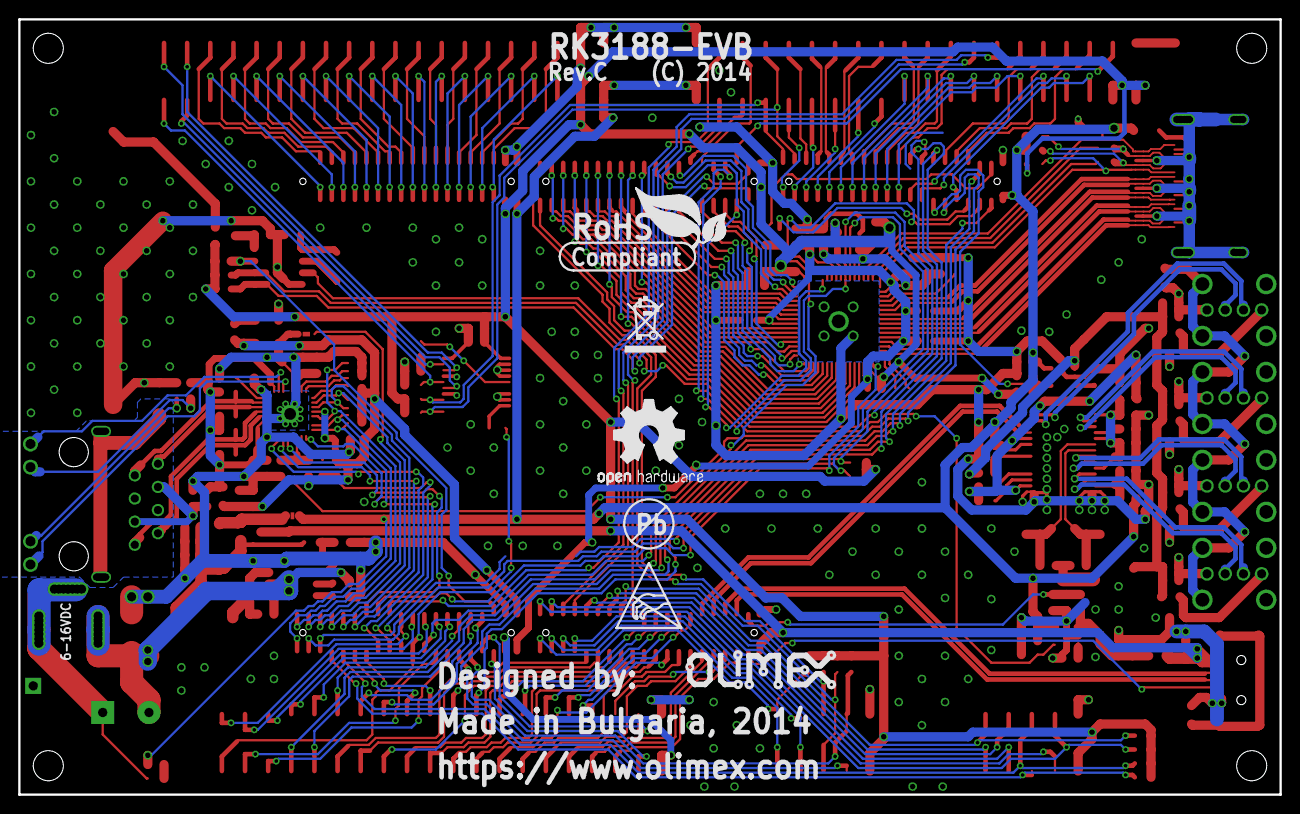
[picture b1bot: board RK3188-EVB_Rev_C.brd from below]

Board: 2 copper layers, 138.4 x 85.1 mm, 191 parts (6 on the bottom side), 277 nets.

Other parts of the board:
U$2: LOGO-OPENHARDWARE_8X8
U$3: OLIMEX1_V
U$9: PB
U$10: ESD_SYMBOL
U$11: RECYCLE_BIN1/8
U$12: ROHS

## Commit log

2024-09-17 LOKUM BOOK ARM LINUX VE ANDROID NOTEBOOK
    ROCKCHIP RK3188,RK3399 VE RK3588S CPU MODELLERİ
    SİSTEM TASARIM MURAT IRKAN 2024/02_09
2024-09-17 LOKUMBOOK.md
2024-09-17 LOKUM 3D RESİM

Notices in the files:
LOKUM BOOK R5-R3 VE R1/RK3188-EVB_Rev_C.brd:
(C) 2014
